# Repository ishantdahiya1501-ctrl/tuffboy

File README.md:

# TuffBoy
**NOTE for admin** : I have been working on this project form then 70+ hrs i have made so much progress and learned so many things you asked me add the things like bom and how will the make this those things are now added also your review stats that "Some of your journals although they have what you've done, kind of doesn't justify why you got the hours and has a brief explanation" I understand that you need proper journals and all i have tried to make the journals bigger and they describe what i did but thee main problem i myself does not remember what i did like 2 or 3 weeks ago that's why i can't full full fill your journal criteria also you guys states that the hours does not justify tbh i am very very new in this tech field i learned kicad from ground zero that's why it takes time to make the pcb to find the parts for the pcb design i am not a pro at the end so if you check any lapse with the devlog you can see that was working only not afk but my speed has now increased also some of the journals were i shifted to linux the lapse are not there becuase i thought that lookout only works in windows so pls keep that in mind. I really hope that this time my project gets selected.  

A handheld multi-tool inspired by the Flipper Zero, but built around the ESP32-C5 Devkit C with **Dual Band** (2.4GHz + 5Ghz), and a big idea: an expansion port that lets you bolt on a whole second microcontroller (Black Pill, or basically any 3.3V dev board).

This is the part that makes TuffBoy ~200× more flexible than a Flipper — instead of being stuck with only 2.4 GHz WiFi we have a breakthrough with the support of 5GHz, opening the door to WiFi security testing, along with support for plugging in whatever co-processor the task needs.

**TuffBoy so far:**

**Circuit diagram:**

**3d model of the device**

**3d render, of back**

**pcb layout**

**the 4-pin expansion connector**

**Schematic**

## what is this

So the Flipper is cool but it's not that good in base form and expensive, and things like M5 Stacks can't really do proper wifi work (absence of 5GHz). TuffBoy is my take on what that device *should* be:

* **ESP32-C5** as the main brain — wifi 5GHz/2.4GHz + BLE, USB-C
* **nRF24L01+** for 2.4GHz radio stuff
* **CC1101** for sub-GHz (300–928 MHz)

* **TFT** — a 2.8" inch which is fully touch, no button, which makes it look like a small phone.

It's being made with the help of [Hack Club](https://hackclub.com/).

## How to make one:

To make one just see the circuit diagram images and copy it then add the script which is in the firmware folder in the esp32 c5 that's all as simple as you see.
How will i make it i preffer to make this on a zero pcb first that will hlep me fix any problems with the pcb. Also if you want to know the wiring here its is:

## Wiring

### Main Controller

The TuffBoy is built around an **ESP32-C5 DevKit-C**. The TFT, CC1101, and nRF24L01+ modules communicate with the ESP32-C5 using SPI, while the 4-pin JST-SH connector provides a UART expansion interface.

### Pin Assignment

| ESP32-C5 GPIO | Connection | Function |
|---|---|---|
| GPIO 6 | SPI SCK | Shared SPI clock |
| GPIO 7 | SPI MOSI | Shared SPI data output |
| GPIO 2 | SPI MISO | Shared SPI data input |
| GPIO 10 | TFT CS | TFT chip select |
| GPIO 3 | TFT DC | TFT data/command |
| GPIO 4 | TFT RST | TFT reset |
| GPIO 5 | TFT BL | TFT backlight control |
| GPIO 8 | Touch CS | Touch controller chip select |
| GPIO 9 | Touch IRQ | Touch interrupt |
| GPIO 0 | CC1101 CS | CC1101 chip select |
| GPIO 1 | CC1101 GDO0 | CC1101 interrupt/status |
| GPIO 18 | nRF24 CSN | nRF24 chip select |
| GPIO 19 | nRF24 CE | nRF24 chip enable |
| GPIO 20 | nRF24 IRQ | nRF24 interrupt |
| GPIO 21 | UART TX | JST-SH TX |
| GPIO 22 | UART RX | JST-SH RX |

> **Note:** GPIO numbers are the proposed firmware/pinout assignment for TuffBoy. Verify them against the exact ESP32-C5 DevKit-C board and your final PCB before manufacturing.

---

## 2.8" SPI TFT + Touch

The TFT uses the ESP32-C5's SPI bus.

| TFT Pin | ESP32-C5 |
|---|---|
| VCC | 3.3V |
| GND | GND |
| SCK / CLK | GPIO 6 |
| MOSI / SDI | GPIO 7 |
| MISO / SDO | GPIO 2 |
| CS | GPIO 10 |
| DC / RS | GPIO 3 |
| RST | GPIO 4 |
| BL / LED | GPIO 5 |

### Touch Controller

For a typical XPT2046-style SPI touch controller:

| Touch Pin | ESP32-C5 |
|---|---|
| VCC | 3.3V |
| GND | GND |
| T_CLK | GPIO 6 |
| T_DIN | GPIO 7 |
| T_DO | GPIO 2 |
| T_CS | GPIO 8 |
| T_IRQ | GPIO 9 |

The TFT and touch controller share the SPI clock, MOSI and MISO lines. Separate chip-select lines allow the ESP32-C5 to communicate with each device independently.

---

## CC1101

The CC1101 uses the same SPI bus as the TFT and touch controller.

| CC1101 Pin | ESP32-C5 |
|---|---|
| VCC | 3.3V |
| GND | GND |
| SCK | GPIO 6 |
| MOSI / SI | GPIO 7 |
| MISO / SO | GPIO 2 |
| CSN / CS | GPIO 0 |
| GDO0 | GPIO 1 |

The CC1101 SPI bus is shared with the other SPI peripherals. Its dedicated CS pin is used to select the CC1101.

**Important:** The CC1101 module must be operated at the appropriate supply voltage for the specific module. Do not assume a 5V logic interface is safe.

---

## nRF24L01+

The nRF24L01+ also shares the main SPI bus.

| nRF24L01+ Pin | ESP32-C5 |
|---|---|
| VCC | 3.3V |
| GND | GND |
| SCK | GPIO 6 |
| MOSI | GPIO 7 |
| MISO | GPIO 2 |
| CSN | GPIO 18 |
| CE | GPIO 19 |
| IRQ | GPIO 20 |

The nRF24L01+ uses the shared SPI bus while **CSN** and **CE** remain dedicated to the module.

> **Power note:** The nRF24L01+ can be sensitive to supply noise. Place a decoupling capacitor close to the module's VCC and GND pins.

---

## 4-Pin JST-SH Expansion Connector

The 4-pin JST-SH connector provides power and a UART interface for an external 3.3V-compatible microcontroller or expansion board.

| JST-SH Pin | ESP32-C5 | Function |
|---|---|---|
| Pin 1 | GND | Ground |
| Pin 2 | 3.3V | VCC |
| Pin 3 | GPIO 21 | TX |
| Pin 4 | GPIO 22 | RX |

### Connector Layout

JST-SH 4-Pin
```text
┌───────────────┐
│ 1 │ 2 │ 3 │ 4 │
└───────────────┘
  │   │   │   │
  │   │   │   └── RX
  │   │   └────── TX
  │   └────────── 3.3V
  └────────────── GND

```

## the uart extension (the big idea)

Every flipper-clone has the same problem: you get one MCU and that's it. The TuffBoy has an **expansion port for a second microcontroller**:

* plug in a **STM32 Black Pill** (or any dev board that runs on 3.3V logic)
* the ESP32-C5 stays the brain (UI, wifi, displays) and the STM32 becomes a co-processor for whatever you want — real-time tasks, extra peripherals, other radio stacks, whatever you can think of
* the connection is a simple **4-pin jst connector: TX, RX, 3.3V and GND** (J1 on the board) — no special hardware, just serial
* since it's just TX/RX + power, basically any 3.3V board fits — black pill, another xiao, whatever you have lying around

With this we can add basically anything we like, without redesigning the main board every time. New feature = new daughter board / new firmware, not a new device.

## wifi hack firmware (The core idea)

The main focus of the software is my **"wifi hack" firmware** — the whole reason I started this. Wifi security testing is weirdly hard to do on existing pocket tools; the Flipper can't do it properly at all and M5 stacks are clunky for it as both lack a 5GHz radio. The goal is a firmware that makes wifi security testing *easy*, straight from the device UI:

* scan / monitor mode
* deauth + handshake capture workflows
* works on **2.4GHz AND 5GHz** wifi — the esp32-c5 has 5GHz wifi built in, and **basically no pocket tool does 5GHz**. flipper can't, m5 can't. this is the rare one.

**obviously: use it only on networks you own or have permission to test. this is a learning tool, not a crime stick.**

## catching up to the flipper (then passing it)

The flipper has a bunch of stuff mine doesn't (yet). here's the honest status on each:

| feature                           | flipper | tuffboy                                            |
| --------------------------------- | ------- | -------------------------------------------------- |
| sub-ghz radio                     | ✅       | ✅ already on board (cc1101)                        |
| 2.4GHz radio                      | ✅       | ✅ already on board (nrf24l01+)                     |
| wifi                              | ❌       | ✅ 2.4 + **5GHz** — the thing flipper can't do      |
| stm32 / co-processor expansion    | ❌       | ✅ 4-pin connector already on board                 |
| IR blaster                        | ✅       | 🔜 needs an IR led + receiver on the next rev      |
| RFID 125kHz                       | ✅       | 🔜 needs extra hardware                            |
| NFC 13.56MHz                      | ✅       | 🔜 needs extra hardware                            |
| iButton                           | ✅       | 🔜 1-wire on a gpio, firmware work                 |
| USB HID / badUSB                  | ✅       | 🔜 the c5 has native usb, so this is firmware-only |
| U2F security key                  | ✅       | 🔜 same, firmware work                             |
| open expansion for any 3.3v board | ❌       | ✅                                                  |

So the plan: everything the flipper does gets added over a few board revs + firmware, and the flipper literally can't do wifi (or take a second mcu) — that's where tuffboy stays ahead.

## software status

The project currently has two firmware paths. You can either use the included TuffBoy starter/custom firmware or clone Bruce and continue from that firmware project.

### Use the TuffBoy firmware

The native starter firmware is located at [`firmware/TuffBoy/TuffBoy.ino`](firmware/TuffBoy/TuffBoy.ino). It is written for the ESP32-C5 Arduino framework and currently provides:

* boot diagnostics and chip information
* configurable LED status indicator
* expansion UART test messages
* I2C bus scanning
* Wi-Fi station mode and nearby-network scanning
* a serial command interface (`help`, `status`, `wifi`, `i2c`, `led`, and more)

The LED, I2C, and expansion UART pins are defined as constants at the top of the sketch because the final pin mapping may change between board revisions. The sketch uses the ESP32 Arduino framework APIs and the built-in `Wire` and `WiFi` libraries.

The project also contains custom firmware developed specifically for TuffBoy, which will be used as the project continues beyond the initial hardware testing stage.

### Clone Bruce firmware

The [`firmware/Bruce Firmware Cloner.py`](firmware/Bruce%20Firmware%20Cloner.py) script downloads the [Bruce firmware](https://github.com/pr3y/Bruce) into a `Bruce/` directory. It requires Python 3.7 or newer. Git is used by default, or the `--zip` option can download an archive without Git.

```bash
# Clone Bruce into the current directory
python3 "firmware/Bruce Firmware Cloner.py"

# Shallow clone into a chosen directory
python3 "firmware/Bruce Firmware Cloner.py" -d ~/projects --depth 1

# Download Bruce as a ZIP archive instead of using Git
python3 "firmware/Bruce Firmware Cloner.py" -d ~/projects --zip
```

Useful options are `--branch` for a specific branch and `--deps` to install the Python build dependencies used by Bruce. After cloning, follow Bruce's own board and build instructions in its repository.

## CAD and enclosure

The PCB uses 3D CAD models of the individual components mainly for **visualisation of the PCB and complete assembly**.

The individual component CAD models used in the PCB 3D model were downloaded from **GrabCAD**. These models are used to represent the physical components and their approximate placement in the complete assembly.

The **TuffBoy cover/enclosure was made according to the requirements of the project and the completed PCB**. The cover was made externally according to the required dimensions, component placement and mechanical requirements, and the STEP file was provided for use with the project.

## current progress

* [x] part selection + custom symbols/footprints (esp32_c5 lib: XIAO SMD footprint, cc1101, oled)
* [x] schematic — all blocks placed (mcu, 2 radios, 2 displays, 4 buttons, battery + headers)
* [x] board outline + placement
* [x] first hand-routed nets (radio area, battery area)
* [x] finish routing + ground pour
* [x] decoupling caps
* [x] DRC clean + renders
* [x] stm32 expansion connector on the board (J1 = TX, RX, 3V3, GND)
* [x] PCB design completed
* [x] custom TuffBoy firmware started
* [x] enclosure / cover STEP file

## files

```text
tuffboy/          the kicad 10 project (sch + pcb)
tuffboy.pretty/   third-party libs (xiaosymbols, ssd1306 footprints etc)
CAD/              step models (esp32-c5, nrf24l01, cc1101, oleds, 603040 battery)
images/           pcb renders + board pics
firmware/         TuffBoy custom firmware and Bruce cloning script
BOM.csv           bill of materials
Front Housing.step
Rear Housing.step
assembly(full)-reduced.stl
tuffboy(without case)-reduced.stl
```

Open `tuffboy/tuffboy.kicad_pro` in kicad 10 and you're good.

## BOM

## Bill of Materials

| Component | Qty | Description | Unit Price | Total |
|---|---:|---|---:|---:|
| ESP32-C5-DevKitC-1 | 1 | ESP32-C5 Wi-Fi 6/6E development board | ₹1,339 | ₹1,339 |
| NRF24L01 Breakout | 1 | nRF24L01+ 2.4GHz RF transceiver module | ₹113 | ₹113 |
| CC1101-868MHz Module | 1 | CC1101 868/915MHz Sub-GHz RF module | ₹247 | ₹247 |
| TFT 320x240 | 1 | 2.8" TFT LCD 320×240 touch display | ₹959 | ₹959 |
| TP4056 | 1 | TP4056 Type-C Li-ion battery charging module | ₹16 | ₹16 |
| 18650 Li-Ion Battery | 4 | 3.7V Li-Ion battery | ₹122 | ₹488 |
| UART Connector | 1 | 4-pin JST connector for expansion/UART | ₹2 | ₹2 |
| Zero PCB | 5 | Perfboard used for initial PCB prototyping | ₹29 | ₹145 |
| Soldering Kit | 1 | Adjustable soldering station/kit | ₹1,399 | ₹1,399 |
| Jumper Cables | 2 | Jumper wire sets for prototyping and wiring | ₹159 | ₹318 |
| Soldering Stand | 1 | Helping-hand soldering stand with magnifier | ₹694 | ₹694 |
| Soldering Wick | 2 | Desoldering braid | ₹18 | ₹36 |
| JST Female Connector | 2 | 4-pin JST connector with wires | ₹13 | ₹26 |
| **Total** | | | | **₹5,782** |

### Estimated Project Cost

**Total: ₹5,782 INR**  
**Approximately: $60.27 USD**

> Prices are approximate and may change depending on availability, shipping, taxes, and seller pricing.
> Buy links are in BOM.csv

## credits

* completely made by ishant dahiya
* inspired by the [Flipper Zero](https://flipperzero.one/) (obviously)
* [Hack Club](https://hackclub.com/) for the support
* individual component CAD models sourced from **GrabCAD** for PCB visualisation
* TuffBoy cover/enclosure made according to the project requirements and provided as a STEP file

## Images

| Image                                     | Description                   |
| ----------------------------------------- | ----------------------------- |
|               | 3D model of the device        |
|          | USB-C connector detail        |
|                 | PCB layout                    |
|                 | Schematic                     |
|                 | Top view of the device        |
|                   | SD card slot                  |
|  | Back cover                    |
|    | 3D render of back             |
|    | Top cover                     |
|    | 4-pin JST expansion connector |
|               | Back view of the device       |

---

*hardware: PCB completed · software: custom firmware in development · last updated Sep 2026*

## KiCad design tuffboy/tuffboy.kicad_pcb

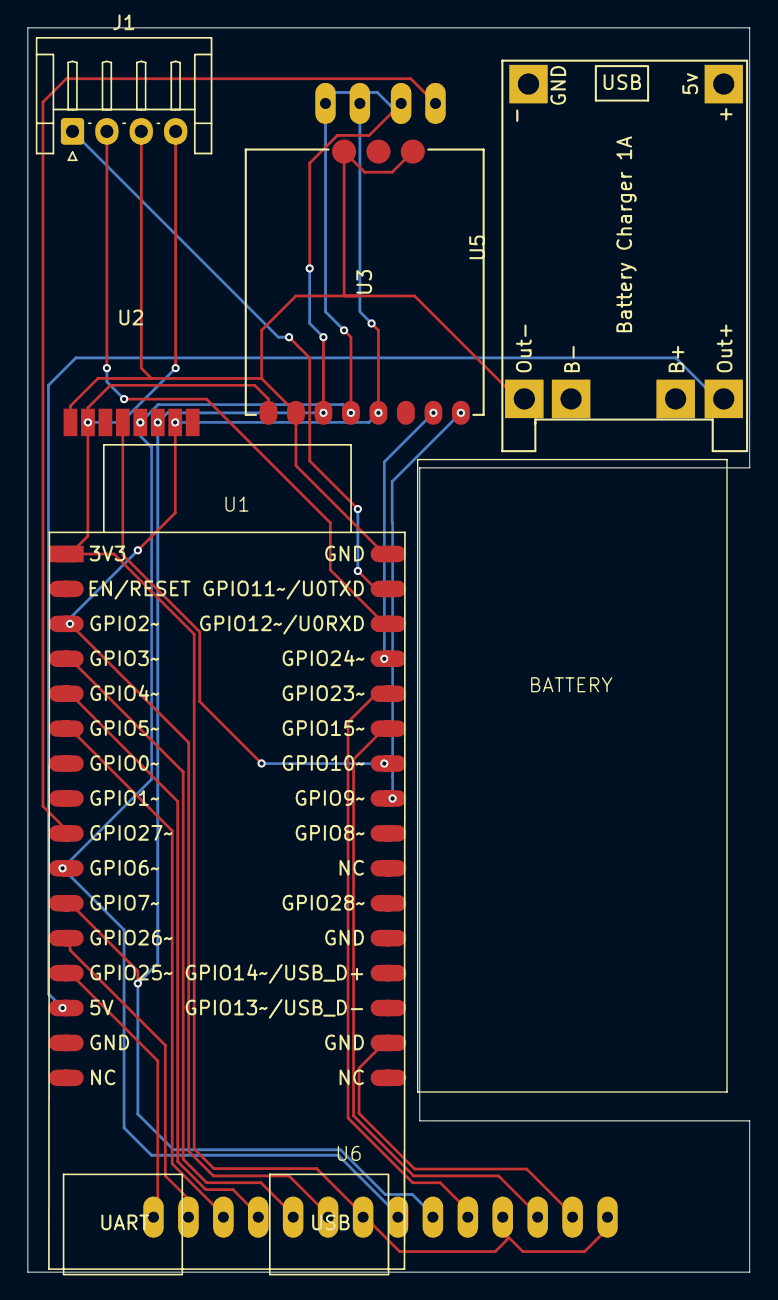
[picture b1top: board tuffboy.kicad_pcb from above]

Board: 2 copper layers, 52.5 x 90.5 mm, 7 parts (1 on the bottom side), 20 nets.

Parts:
J1: Conn_01x04_Pin; JST_EH_S4B-EH_1x04_P2.50mm_Horizontal
U1: ESP32-C5-DevKitC-1
U2: NRF24L01_Breakout; NRF24L01-SMD
U3: CC1101-868MHz-Module
U4: TFT_320x240; TFT-320x240
U5: TP4056-18650
U6: battery

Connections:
/3.3v: J1.4, U1.1 (3V3), U2.2 (VCC), U3.1 (VCC), U4.1 (VCC), U4.4 (RST), U4.8 (LED)
/5v: U1.14 (5V), U5.3 (OUT+)
/CS: U1.27 (GPIO15), U4.3 (CS)
/CS1: U1.9 (GPIO27), U4.15 (SD_CS)
/CSN: U1.26 (GPIO10), U2.4 (~CSN)
/CSN1: U1.25 (GPIO9), U3.8 (CSN)
/DC: U1.28 (GPIO23), U4.5 (DC)
/GDO0: U1.29 (GPIO24), U3.7 (GDO0)
/GND: J1.3, U1.32 (GND), U2.1 (GND), U3.2 (GND), U3.9 (GND), U3.11 (GND), U5.4 (OUT-)
/GND_1: U1.18 (GND), U4.2 (GND)
/MISO: U1.3 (GPIO2/MTMS), U2.7 (MISO), U3.5 (MISO), U4.9 (MISO), U4.17 (SD_MISO)
/MOSI: U1.11 (GPIO7), U2.6 (MOSI), U3.3 (MOSI), U4.6 (MOSI), U4.16 (SD_MOSI)
/RX: J1.2, U1.30 (GPIO12/U0RXD)
/SCLK: U1.10 (GPIO6), U2.5 (SCK), U3.4 (SCLK), U4.7 (SCK), U4.18 (SD_SCK)
/TX: J1.1, U1.31 (GPIO11/U0TXD)
/T_CLK: U1.4 (GPIO3/MTDI), U4.10 (T_CLK)
/T_CS: U1.5 (GPIO4/MTCK), U4.11 (T_CS)
/T_DIN: U1.6 (GPIO5/MTDO), U4.12 (T_DIN)
/T_DO: U1.12 (GPIO26), U4.13 (T_DO)
/T_IRQ: U1.13 (GPIO25), U4.14 (T_IRQ)
